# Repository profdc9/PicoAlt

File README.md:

# Pico Alt

This is a simplified Pi Pico board that can be fabricated by JLCPCB.  I customized it to add more flash, a linear regulator, and to be easier to modify if needed.

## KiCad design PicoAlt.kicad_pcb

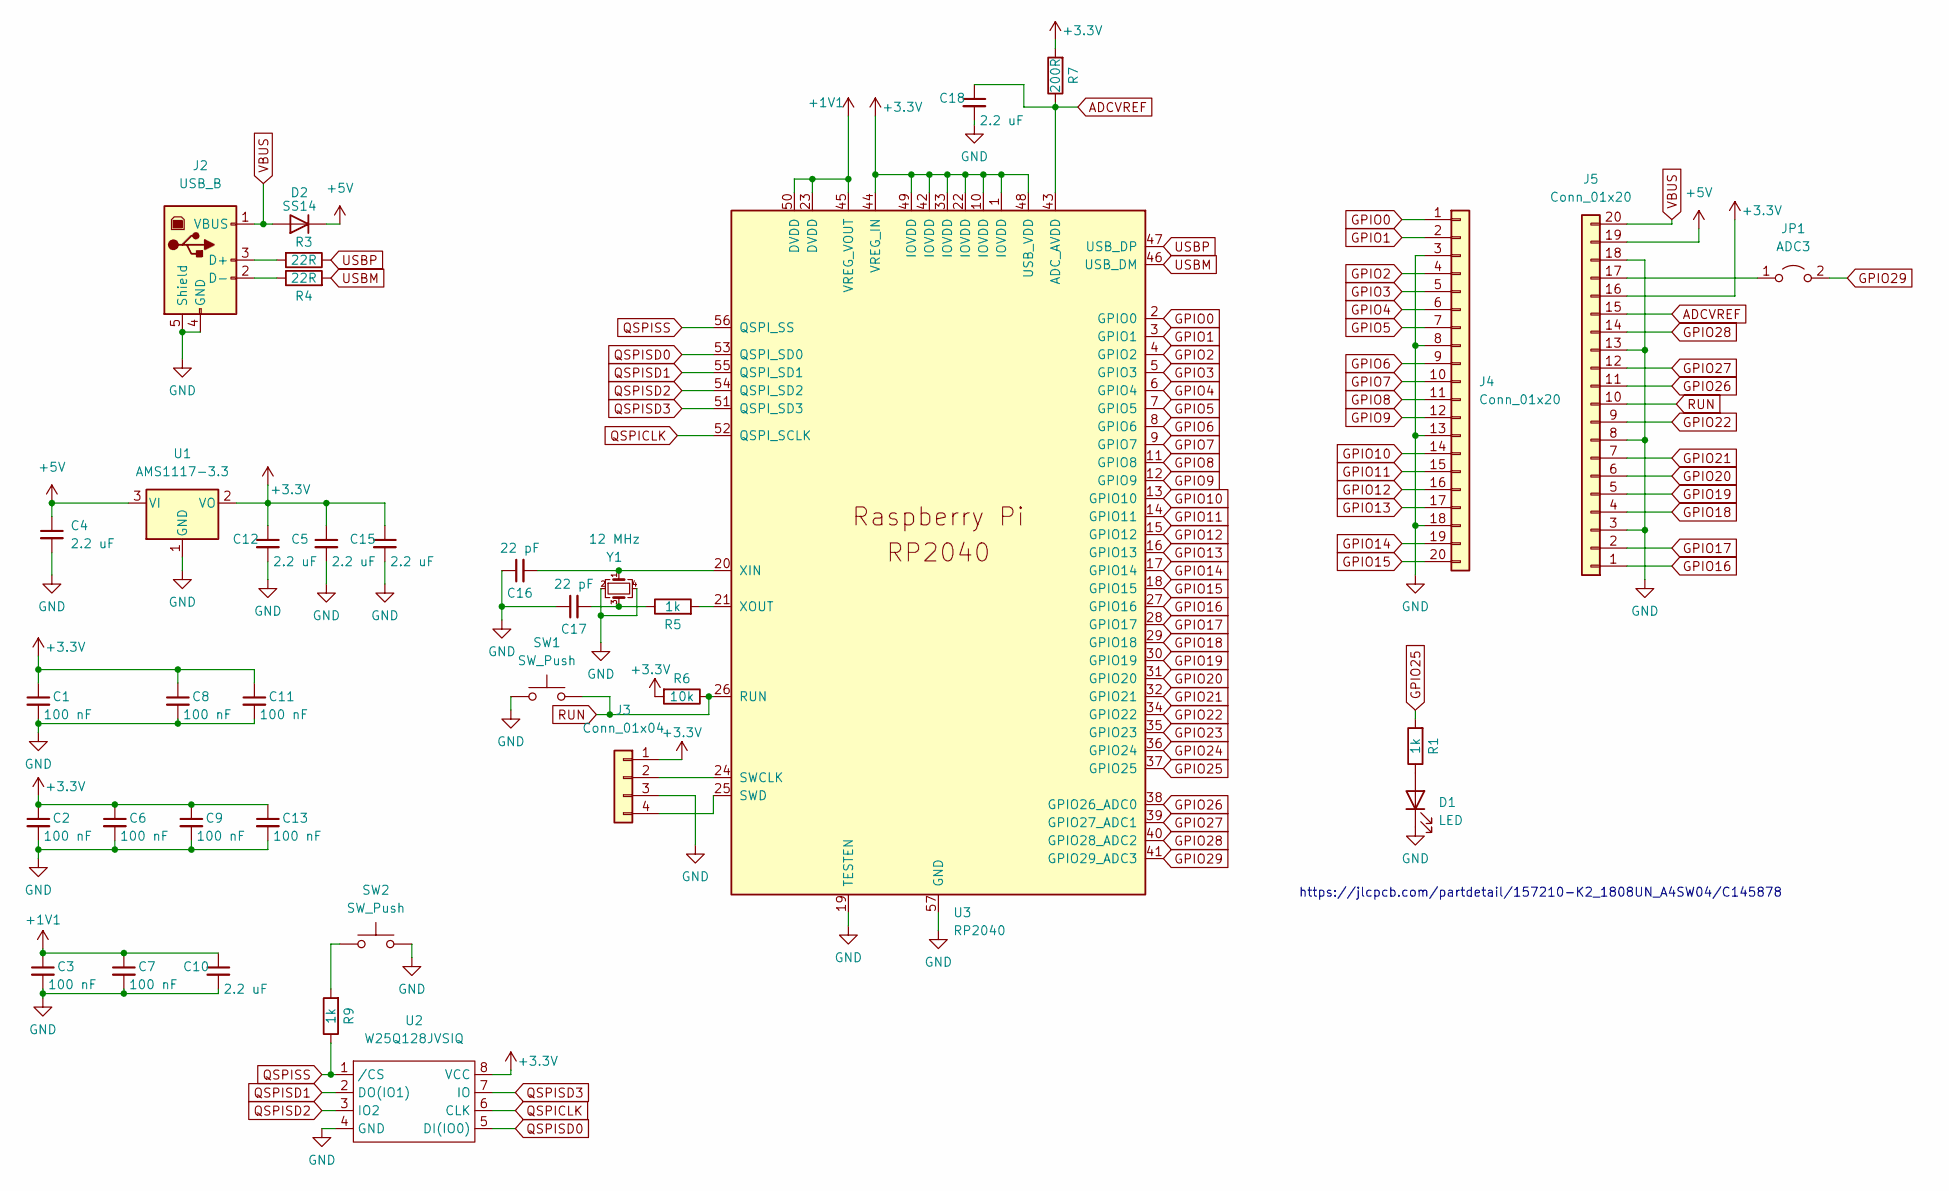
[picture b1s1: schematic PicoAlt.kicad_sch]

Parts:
C1, C2, C3, C6, C7, C8, C9, C11, C13: 100 nF; C_0402_1005Metric; LCSC C307331
C4, C5, C10, C12, C15, C18: 2.2 uF; C_0603_1608Metric; LCSC C23630
C16, C17: 22 pF; C_0402_1005Metric; LCSC C1555
D1: LED; LED_0603_1608Metric_Pad1.05x0.95mm_HandSolder; LCSC C2286
D2: SS14; D_SMA; LCSC C2480
J2: USB_B; USB_B_OST_USB-B1HSxx_Horizontal
J3: Conn_01x04; PinHeader_1x04_P2.54mm_Vertical
J4, J5: Conn_01x20; PinHeader_1x20_P2.54mm_Vertical
JP1: ADC3; PinHeader_1x02_P2.54mm_Vertical
R1, R5, R9: 1k; R_0603_1608Metric_Pad0.98x0.95mm_HandSolder; LCSC C21190
R3, R4: 22R; R_0603_1608Metric_Pad0.98x0.95mm_HandSolder; LCSC C23345
R6: 10k; R_0603_1608Metric_Pad0.98x0.95mm_HandSolder; LCSC C25804
R7: 200R; R_0603_1608Metric_Pad0.98x0.95mm_HandSolder; LCSC C22962
SW1, SW2: SW_Push; K2-1808UN; LCSC C145878
U1: AMS1117-3.3; SOT-223-3_TabPin2; LCSC C6186
U2: W25Q128JVSIQ; SOIC-8_3.9x4.9mm_P1.27mm_mod
U3: RP2040; QFN-56-1EP_7x7mm_P0.4mm_EP3.2x3.2mm; LCSC C2040
Y1: 12 MHz; Crystal_SMD_3225-4Pin_3.2x2.5mm; LCSC C9002

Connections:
+1V1: C3.1, C7.1, C10.1, U3.23 (DVDD), U3.45 (VREG_VOUT), U3.50 (DVDD)
+3.3V: C1.1, C2.1, C5.1, C6.1, C8.1, C9.1, C11.1, C12.1, C13.1, C15.1, J3.1, J5.16, R6.2, R7.2, U1.2 (VO), U2.8 (VCC), U3.1 (IOVDD), U3.10 (IOVDD), U3.22 (IOVDD), U3.33 (IOVDD), U3.42 (IOVDD), U3.44 (VREG_IN), U3.48 (USB_VDD), U3.49 (IOVDD)
+5V: C4.1, D2.1 (K), J5.19, U1.3 (VI)
ADCVREF: C18.1, J5.15, R7.1, U3.43 (ADC_AVDD)
GND: C1.2, C2.2, C3.2, C4.2, C5.2, C6.2, C7.2, C8.2, C9.2, C10.2, C11.2, C12.2, C13.2, C15.2, C16.1, C17.1, C18.2, D1.1 (K), J2.4 (GND), J2.5 (Shield), J3.3, J4.3, J4.8, J4.13, J4.18, J5.3, J5.8, J5.13, J5.18, SW1.1, SW2.2, U1.1 (GND), U2.4 (GND), U3.19 (TESTEN), U3.57 (GND), Y1.2, Y1.4
GPIO0: J4.1, U3.2 (GPIO0)
GPIO1: J4.2, U3.3 (GPIO1)
GPIO2: J4.4, U3.4 (GPIO2)
GPIO3: J4.5, U3.5 (GPIO3)
GPIO4: J4.6, U3.6 (GPIO4)
GPIO5: J4.7, U3.7 (GPIO5)
GPIO6: J4.9, U3.8 (GPIO6)
GPIO7: J4.10, U3.9 (GPIO7)
GPIO8: J4.11, U3.11 (GPIO8)
GPIO9: J4.12, U3.12 (GPIO9)
GPIO10: J4.14, U3.13 (GPIO10)
GPIO11: J4.15, U3.14 (GPIO11)
GPIO12: J4.16, U3.15 (GPIO12)
GPIO13: J4.17, U3.16 (GPIO13)
GPIO14: J4.19, U3.17 (GPIO14)
GPIO15: J4.20, U3.18 (GPIO15)
GPIO16: J5.1, U3.27 (GPIO16)
GPIO17: J5.2, U3.28 (GPIO17)
GPIO18: J5.4, U3.29 (GPIO18)
GPIO19: J5.5, U3.30 (GPIO19)
GPIO20: J5.6, U3.31 (GPIO20)
GPIO21: J5.7, U3.32 (GPIO21)
GPIO22: J5.9, U3.34 (GPIO22)
GPIO23: U3.35 (GPIO23)
GPIO24: U3.36 (GPIO24)
GPIO25: R1.2, U3.37 (GPIO25)
GPIO26: J5.11, U3.38 (GPIO26_ADC0)
GPIO27: J5.12, U3.39 (GPIO27_ADC1)
GPIO28: J5.14, U3.40 (GPIO28_ADC2)
GPIO29: JP1.2 (B), U3.41 (GPIO29_ADC3)
unnamed: C16.2, U3.20 (XIN), Y1.1
unnamed: C17.2, R5.1, Y1.3
unnamed: D1.2 (A), R1.1
unnamed: J2.2 (D-), R4.1
unnamed: J2.3 (D+), R3.2
unnamed: J3.2, U3.24 (SWCLK)
unnamed: J3.4, U3.25 (SWD)
unnamed: J5.17, JP1.1 (A)
unnamed: R5.2, U3.21 (XOUT)
unnamed: R9.2, SW2.1
QSPICLK: U2.6 (CLK), U3.52 (QSPI_SCLK)
QSPISD0: U2.5 (DI(IO0)), U3.53 (QSPI_SD0)
QSPISD1: U2.2 (DO(IO1)), U3.55 (QSPI_SD1)
QSPISD2: U2.3 (IO2), U3.54 (QSPI_SD2)
QSPISD3: U2.7 (IO), U3.51 (QSPI_SD3)
QSPISS: R9.1, U2.1 (/CS), U3.56 (QSPI_SS)
RUN: J5.10, R6.1, SW1.2, U3.26 (RUN)
USBM: R4.2, U3.46 (USB_DM)
USBP: R3.1, U3.47 (USB_DP)
VBUS: D2.2 (A), J2.1 (VBUS), J5.20

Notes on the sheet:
https://jlcpcb.com/partdetail/157210-K2_1808UN_A4SW04/C145878

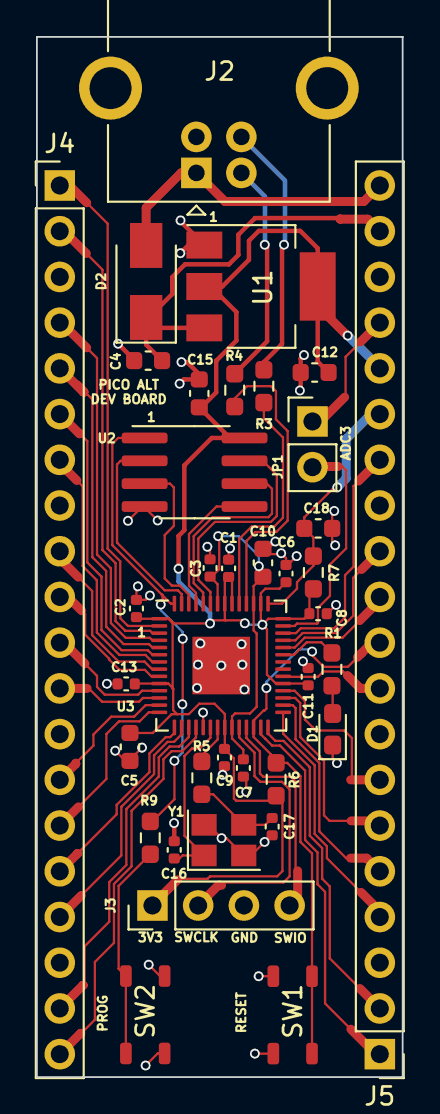
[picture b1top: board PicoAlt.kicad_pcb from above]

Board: 2 copper layers, 20.3 x 57.8 mm, 37 parts (0 on the bottom side), 53 nets.

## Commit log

2024-02-24 JLCPCB submit
2024-02-24 Modified for bigger SOIC-8 footprint
2024-02-26 JLCPCB #2
2024-03-13 Added photo
